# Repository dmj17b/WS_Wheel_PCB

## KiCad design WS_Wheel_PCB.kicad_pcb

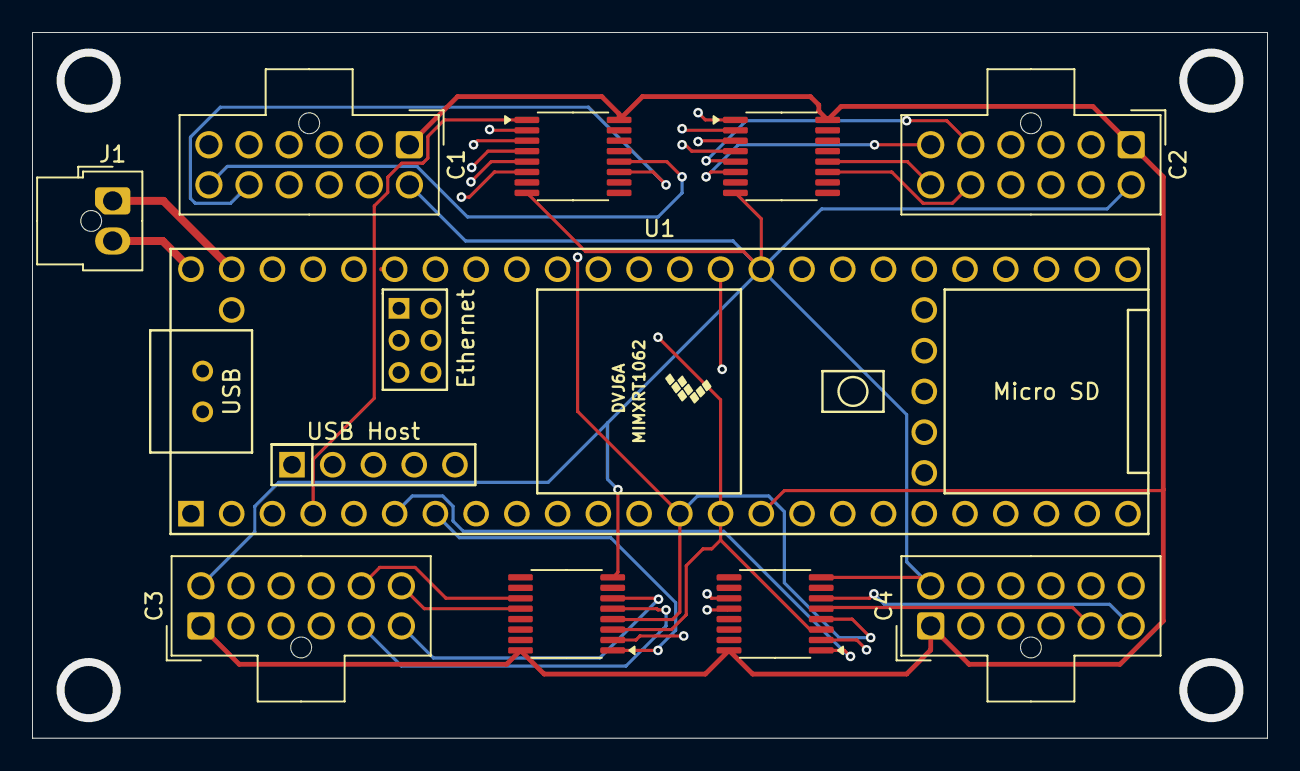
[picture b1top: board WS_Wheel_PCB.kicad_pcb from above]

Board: 4 copper layers, 77.0 x 44.0 mm, 10 parts (0 on the bottom side), 51 nets.

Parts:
C1, C2, C3, C4: Molex_Nano-Fit_105310-xx12_2x06_P2.50mm_Vertical
J1: 5V in; Molex_Nano-Fit_105309-xx02_1x02_P2.50mm_Vertical
LS1, LS2, LS3, LS4: LS7466
U1: Teensy4.1; Teensy41

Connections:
unnamed: C1.1 (3v3), C2.1 (3v3), C3.1 (3v3), C4.1 (3v3), LS1.16 (VDD), LS2.16 (VDD), LS3.16 (VDD), LS4.16 (VDD), U1.15 (3V3)
unnamed: C1.3 (DirAx), U1.44 (22_A8_CTX1)
unnamed: C1.9 (DirAy), U1.9 (7_RX2_OUT1A)
unnamed: C1.4 (DirBx), U1.43 (21_A7_RX5_BCLK1)
unnamed: C1.10 (DirBy), U1.10 (8_TX2_IN1)
unnamed: C1.2 (ENx), U1.45 (23_A9_CRX1_MCLK1)
unnamed: C1.8 (ENy), U1.8 (6_OUT1D)
unnamed: C1.5 (EncAx), LS1.5 (Ax)
unnamed: C1.11 (EncAy), LS1.11 (Ay)
unnamed: C1.6 (EncBx), LS1.6 (Bx)
unnamed: C1.12 (EncBy), LS1.12 (By)
unnamed: C1.7 (GND), C2.7 (GND), C3.7 (GND), C4.7 (GND), LS1.8 (GND), LS2.8 (GND), LS3.8 (GND), LS4.8 (GND), U1.34 (GND)
unnamed: C2.3 (DirAx), U1.41 (19_A5_SCL)
unnamed: C2.9 (DirAy), U1.17 (25_A11_RX6_SDA2)
unnamed: C2.4 (DirBx), U1.40 (18_A4_SDA)
unnamed: C2.10 (DirBy), U1.18 (26_A12_MOSI1)
unnamed: C2.2 (ENx), U1.42 (20_A6_TX5_LRCLK1)
unnamed: C2.8 (ENy), U1.16 (24_A10_TX6_SCL2)
unnamed: C2.5 (EncAx), LS2.5 (Ax)
unnamed: C2.11 (EncAy), LS2.11 (Ay)
unnamed: C2.6 (EncBx), LS2.6 (Bx)
unnamed: C2.12 (EncBy), LS2.12 (By)
unnamed: C3.3 (DirAx), U1.38 (16_A2_RX4_SCL1)
unnamed: C3.9 (DirAy), U1.20 (28_RX7)
unnamed: C3.4 (DirBx), U1.30 (38_CS1_IN1)
unnamed: C3.10 (DirBy), U1.21 (29_TX7)
unnamed: C3.2 (ENx), U1.39 (17_A3_TX4_SDA1)
unnamed: C3.8 (ENy), U1.19 (27_A13_SCK1)
unnamed: C3.5 (EncAx), LS3.5 (Ax)
unnamed: C3.11 (EncAy), LS3.11 (Ay)
unnamed: C3.6 (EncBx), LS3.6 (Bx)
unnamed: C3.12 (EncBy), LS3.12 (By)
unnamed: C4.3 (DirAx), U1.32 (40_A16)
unnamed: C4.9 (DirAy), U1.23 (31_CTX3)
unnamed: C4.4 (DirBx), U1.31 (39_MISO1_OUT1A)
unnamed: C4.10 (DirBy), U1.24 (32_OUT1B)
unnamed: C4.2 (ENx), U1.33 (41_A17)
unnamed: C4.8 (ENy), U1.22 (30_CRX3)
unnamed: C4.5 (EncAx), LS4.5 (Ax)
unnamed: C4.11 (EncAy), LS4.11 (Ay)
unnamed: C4.6 (EncBx), LS4.6 (Bx)
unnamed: C4.12 (EncBy), LS4.12 (By)
unnamed: J1.1, U1.47 (GND)
unnamed: J1.2, U1.48 (VIN)
unnamed: LS1.3 (MISO), LS2.3 (MISO), LS3.3 (MISO), LS4.3 (MISO), U1.14 (12_MISO_MQSL)
unnamed: LS1.4 (MOSI), LS2.4 (MOSI), LS3.4 (MOSI), LS4.4 (MOSI), U1.13 (11_MOSI_CTX1)
unnamed: LS1.2 (SCK), LS2.2 (SCK), LS3.2 (SCK), LS4.2 (SCK), U1.35 (13_SCK_LED)
unnamed: LS1.1 (SS/), U1.4 (2_OUT2)
unnamed: LS2.1 (SS/), U1.5 (3_LRCLK2)
unnamed: LS3.1 (SS/), U1.7 (5_IN2)
unnamed: LS4.1 (SS/), U1.6 (4_BCLK2)

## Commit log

2025-03-04 Basic custom components created
2025-03-10 Making progress
2025-03-11 Starting over bc new voltage reqs
2025-03-12 Saving for the day
2025-04-22 Final?
2025-04-29 pushing
2025-05-28 Starting V2
